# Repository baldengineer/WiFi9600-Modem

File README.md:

# WiFi9600 Modem
 Retro-cyling a Practical Peripherals 9600SA into a WiFiModem

Design files and code for WiFi9600.

As a kid, I had a Practical Peripherals 9600SA. For years I used it to connect to BBSes and then the Internet. At least, until I upgraded to a 56K USR Sportser.

This project removes the original electronics and replaces them with an ESP8266, MP3 Player, and some relays. It allows classic computers with a RS-232 port to connect to the internet via telnet. 

The MP3 player enables authentic fake modem sounds. And the relays are there for authentic real clicky-clicks.

Live stream archive of the project work is available here:
https://www.twitch.tv/baldengineer/videos

Watch the stream and help out in chat here:
https://twitch.tv/baldengineer

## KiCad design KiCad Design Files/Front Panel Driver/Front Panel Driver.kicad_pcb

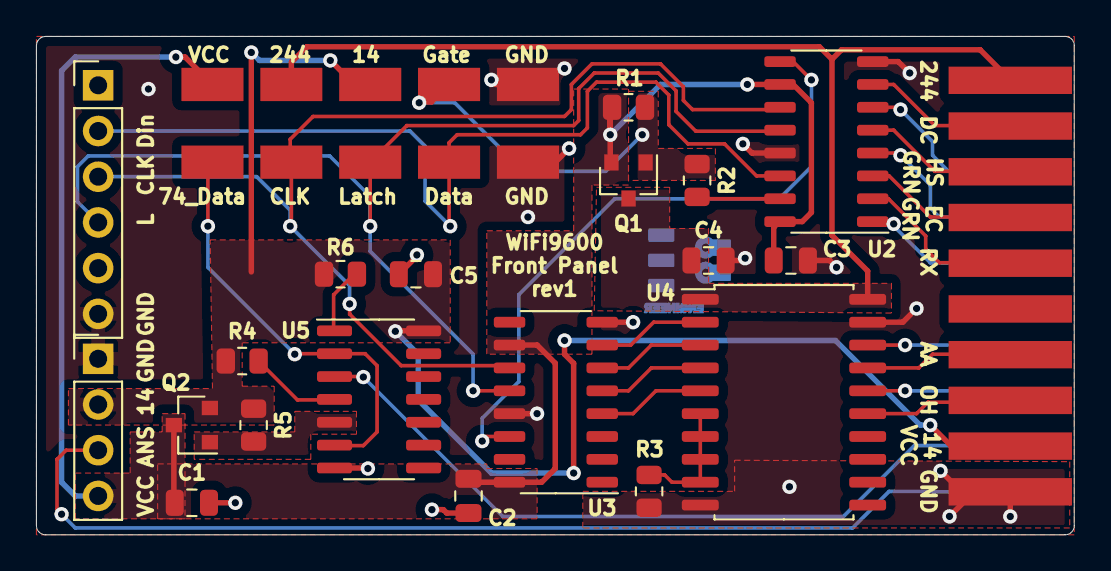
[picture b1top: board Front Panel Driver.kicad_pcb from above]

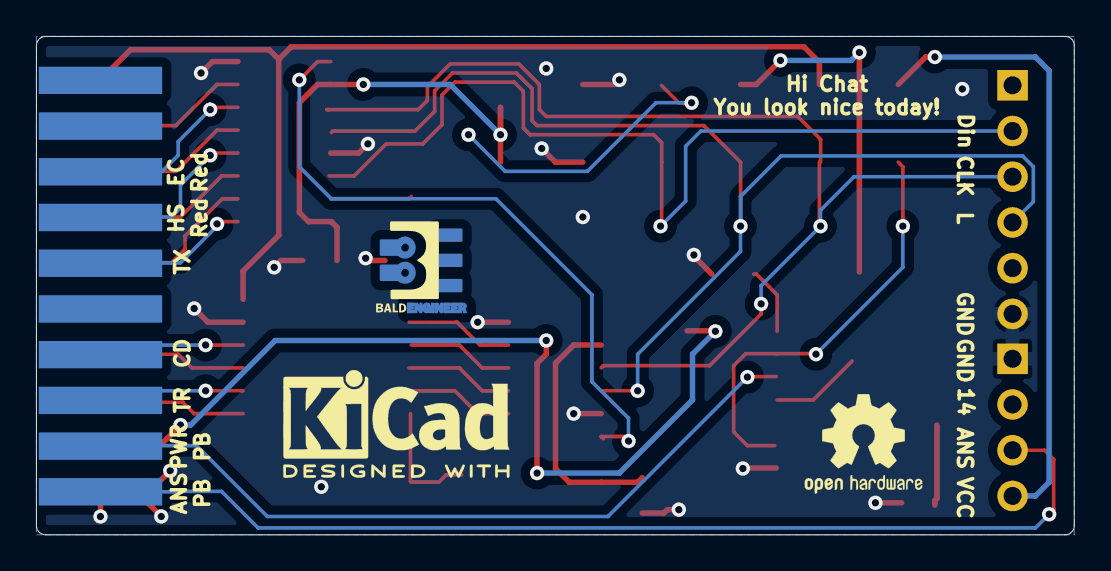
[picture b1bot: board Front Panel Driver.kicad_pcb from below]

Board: 2 copper layers, 57.7 x 27.7 mm, 31 parts (2 on the bottom side), 32 nets.

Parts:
C1, C2, C3, C4, C5: 1uF; C_0805_2012Metric
J9: Front_Panel; Edge_10mil_2x10
J10: PWR_HDR; PinHeader_1x04_P2.54mm_Vertical
J11: SH_HDR; PinHeader_1x06_P2.54mm_Vertical
Q1, Q2: P-NMOS; SOT-23
R1, R3, R4, R5, R6: 4k7; R_0805_2012Metric
R2: 1k; R_0805_2012Metric
TP1: TP_Panel_EN; Harwin-S1751-46-Test-Point
TP2: TP_244_VCC; Harwin-S1751-46-Test-Point
TP3: Data; Harwin-S1751-46-Test-Point
TP4: Clock; Harwin-S1751-46-Test-Point
TP5: Latch; Harwin-S1751-46-Test-Point
TP6: TP_74_Data; Harwin-S1751-46-Test-Point
TP7: TP_14_VCC; Harwin-S1751-46-Test-Point
TP8: TP_VCC; Harwin-S1751-46-Test-Point
TP9: TP_GND1; Harwin-S1751-46-Test-Point
TP10: TP_GND2; Harwin-S1751-46-Test-Point
U2, U3: 74HCT595; SO-16_3.9x9.9mm_P1.27mm
U4: 74HCT245; SOIC-20W_7.5x12.8mm_P1.27mm
U5: 74HCT74; SOIC-14_3.9x8.7mm_P1.27mm
svg2mod: G***; BE5

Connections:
/14-VCC: C5.1, J9.12, J10.2, Q2.2, R4.1, R5.1, R6.2, TP7.1, U5.14
/244-VCC: C4.1, J9.20, Q1.3, TP2.1, U4.1, U4.20
/AA: J9.14, U4.17
/ANS-PB: J9.10, J10.3
/CD: J9.7, U4.18
/DC: J9.19, U2.7
/Data-In: J11.2, TP3.1, U2.14
/EC-GRN: J9.17, U2.3
/EC-Red: J9.3, U2.6
/FF-DATA: TP6.1, U5.2, U5.6
/Gate244: Q1.1, R1.1, R2.1, TP1.1
/HS-GRN: J9.18, U2.5
/HS-Red: J9.4, U2.4
/Latch: J11.4, TP5.1, U2.12, U3.12
/OH: J9.13, U4.15
/PWR-PB: J9.9, U5.3
/Panel-En: R2.2, U2.15
/RX: J9.16, U2.2
/SH1: U3.4, U4.5
/SH2: U3.5, U4.4
/SH3: U3.6, U4.3
/SH4: U3.7, U4.2
/SH-Carry: U2.9, U3.14
/Ser-Clock: J11.3, TP4.1, U2.11, U3.11
/TR: J9.8, U4.16
/TX: J9.5, U2.1
GND: C1.2, C2.2, C3.2, C4.2, C5.2, J9.11, J10.1, J11.6, R3.2, TP9.1, TP10.1, U2.8, U2.13, U3.8, U3.13, U4.10, U4.19, U5.7
unnamed: Q2.1, R5.2, U5.5
unnamed: R3.1, U4.6, U4.7, U4.8, U4.9
unnamed: R4.2, U5.4
unnamed: R6.1, U5.1
VCC: C1.1, C2.1, C3.1, J10.4, Q1.2, Q2.3, R1.2, TP8.1, U2.10, U2.16, U3.10, U3.16

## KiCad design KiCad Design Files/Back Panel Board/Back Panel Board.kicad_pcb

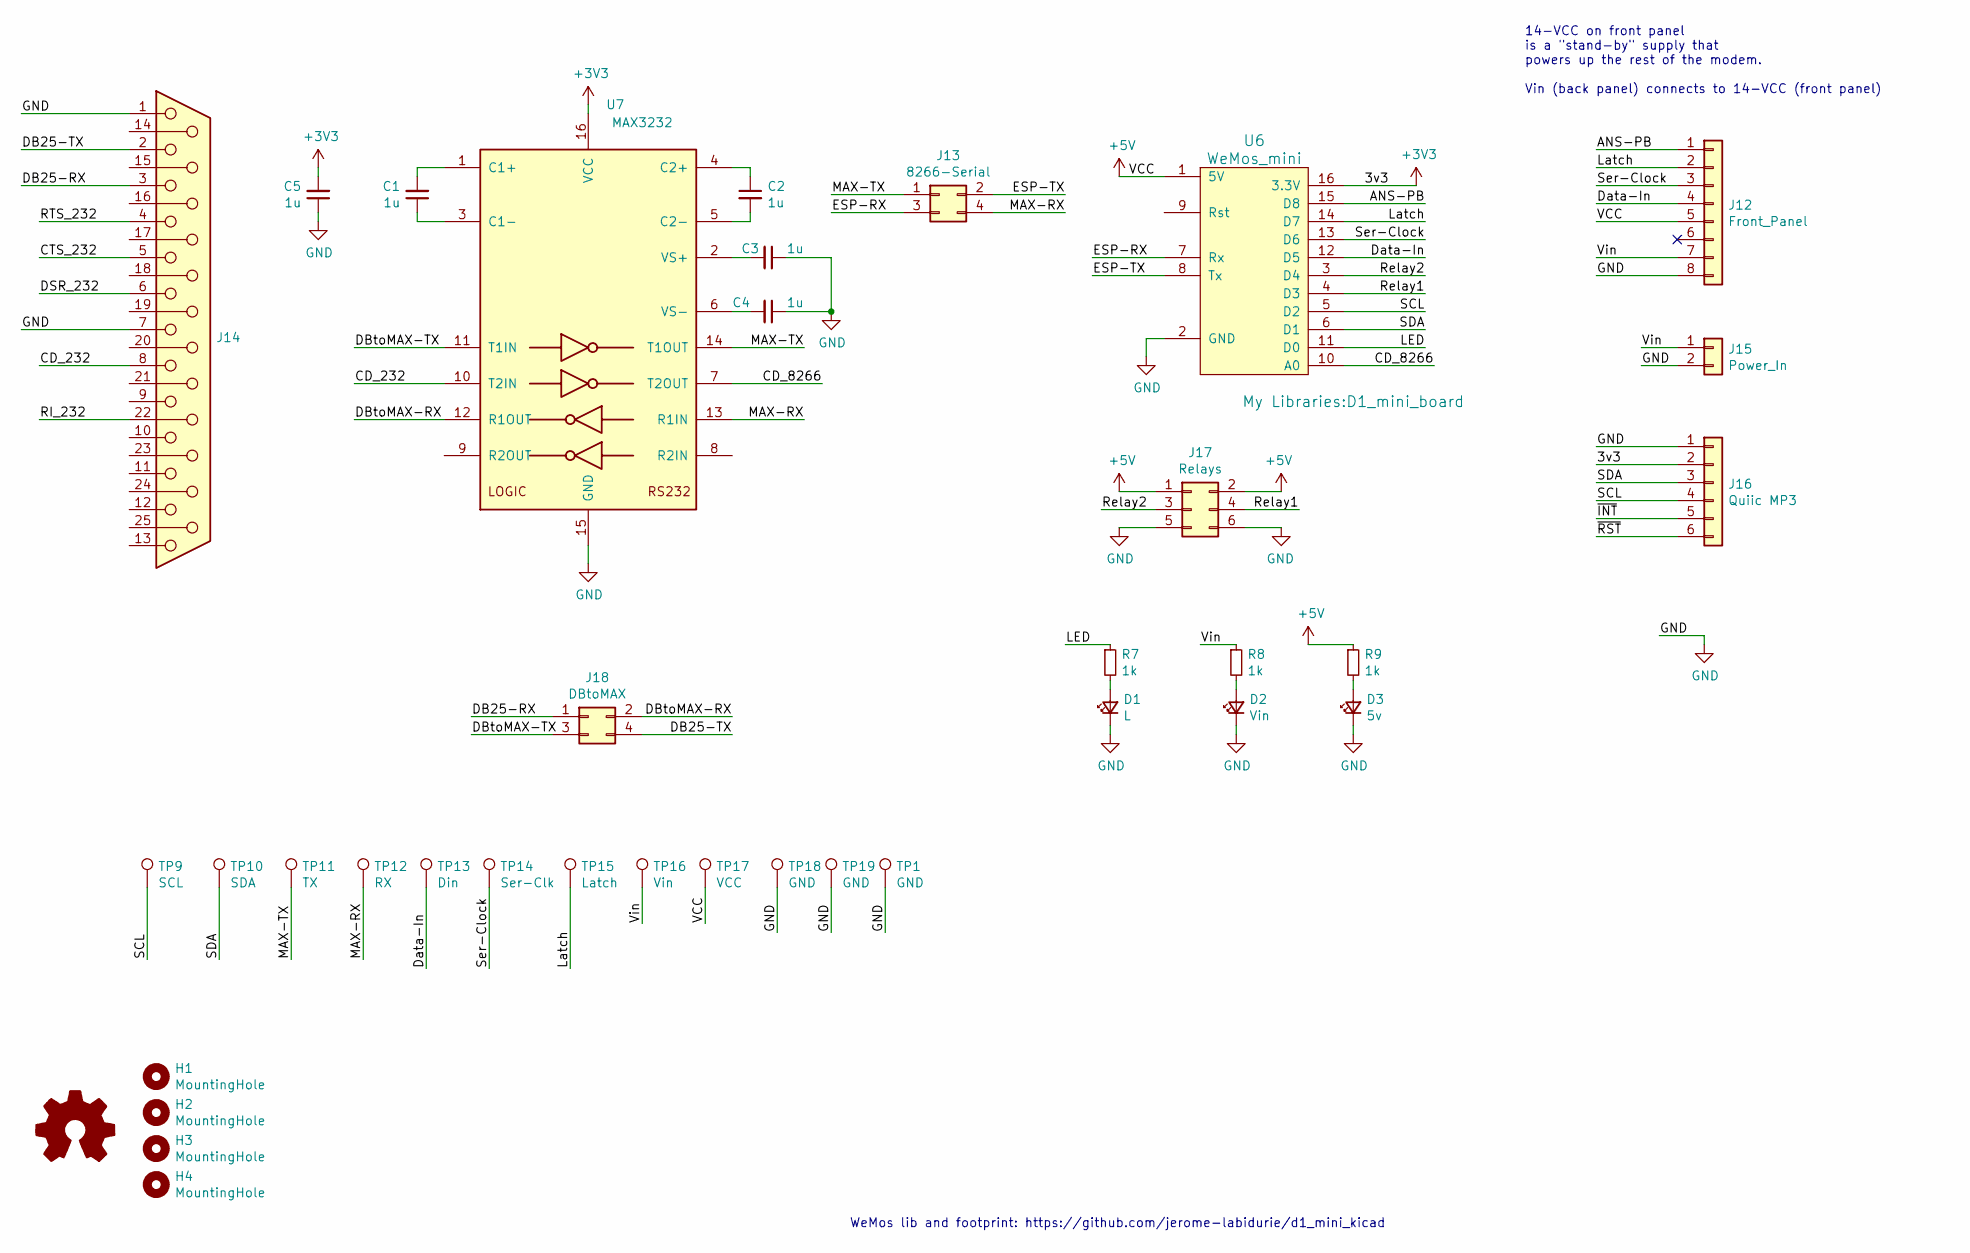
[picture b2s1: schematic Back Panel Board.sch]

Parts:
C1, C2, C3, C4, C5: 1u; C_0805_2012Metric
D1: L; LED_1206_3216Metric
D2: Vin; LED_1206_3216Metric
D3: 5v; LED_1206_3216Metric
H1, H2, H3, H4: MountingHole; MountingHole_2.5mm
J12: Front_Panel; PinHeader_1x08_P2.54mm_Vertical
J13: 8266-Serial; PinHeader_2x02_P2.54mm_Vertical
J14: DB25_Female_MountingHoles; DSUB-25_Female_EdgeMount_P2.77mm
J15: Power_In; PinHeader_1x02_P2.54mm_Vertical
J16: Quiic MP3; PinHeader_1x06_P2.54mm_Vertical
J17: Relays; PinHeader_2x03_P2.54mm_Vertical
J18: DBtoMAX; PinHeader_2x02_P2.54mm_Vertical
R7, R8, R9: 1k; R_0805_2012Metric
TP1, TP18, TP19: GND; Harwin-S1751-46-Test-Point
TP9: SCL; Harwin-S1751-46-Test-Point
TP10: SDA; Harwin-S1751-46-Test-Point
TP11: TX; Harwin-S1751-46-Test-Point
TP12: RX; Harwin-S1751-46-Test-Point
TP13: Din; Harwin-S1751-46-Test-Point
TP14: Ser-Clk; Harwin-S1751-46-Test-Point
TP15: Latch; Harwin-S1751-46-Test-Point
TP16: Vin; Harwin-S1751-46-Test-Point
TP17: VCC; Harwin-S1751-46-Test-Point
U6: WeMos_mini; D1_mini_board
U7: MAX3232; SOIC-16W_7.5x10.3mm_P1.27mm

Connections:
+3V3: C5.2, J16.2, U6.16 (3.3V), U7.16 (VCC)
+5V: J12.5, J17.1, J17.2, R9.1, TP17.1, U6.1 (5V)
/ANS-PB: J12.1, U6.15 (D8)
/CD_232: J14.8, U7.10 (T2IN)
/CD_8266: U6.10 (A0), U7.7 (T2OUT)
/CTS_232: J14.5
/DB25-RX: J14.3, J18.1
/DB25-TX: J14.2, J18.4
/DBtoMAX-RX: J18.2, U7.12 (R1OUT)
/DBtoMAX-TX: J18.3, U7.11 (T1IN)
/DSR_232: J14.6
/Data-In: J12.4, TP13.1, U6.12 (D5)
/ESP-RX: J13.3, U6.7 (Rx)
/ESP-TX: J13.2, U6.8 (Tx)
/LED: R7.1, U6.11 (D0)
/Latch: J12.2, TP15.1, U6.14 (D7)
/MAX-RX: J13.4, TP12.1, U7.13 (R1IN)
/MAX-TX: J13.1, TP11.1, U7.14 (T1OUT)
/RI_232: J14.22
/RTS_232: J14.4
/Relay1: J17.4, U6.4 (D3)
/Relay2: J17.3, U6.3 (D4)
/SCL: J16.4, TP9.1, U6.5 (D2)
/SDA: J16.3, TP10.1, U6.6 (D1)
/Ser-Clock: J12.3, TP14.1, U6.13 (D6)
/Vin: J12.7, J15.1, R8.1, TP16.1
/~INT: J16.5
/~RST: J16.6
GND: C3.1, C4.1, C5.1, D1.1 (K), D2.1 (K), D3.1 (K), J12.8, J14.1, J14.7, J15.2, J16.1, J17.5, J17.6, TP1.1, TP18.1, TP19.1, U6.2 (GND), U7.15 (GND)
unnamed: C1.1, U7.3 (C1-)
unnamed: C1.2, U7.1 (C1+)
unnamed: C2.1, U7.4 (C2+)
unnamed: C2.2, U7.5 (C2-)
unnamed: C3.2, U7.2 (VS+)
unnamed: C4.2, U7.6 (VS-)
unnamed: D1.2 (A), R7.2
unnamed: D2.2 (A), R8.2
unnamed: D3.2 (A), R9.2

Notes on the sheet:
14-VCC on front panel is a "stand-by" supply that powers up the rest of the modem. Vin (back panel) connects to 14-VCC (front panel)
WeMos lib and footprint: https://github.com/jerome-labidurie/d1_mini_kicad

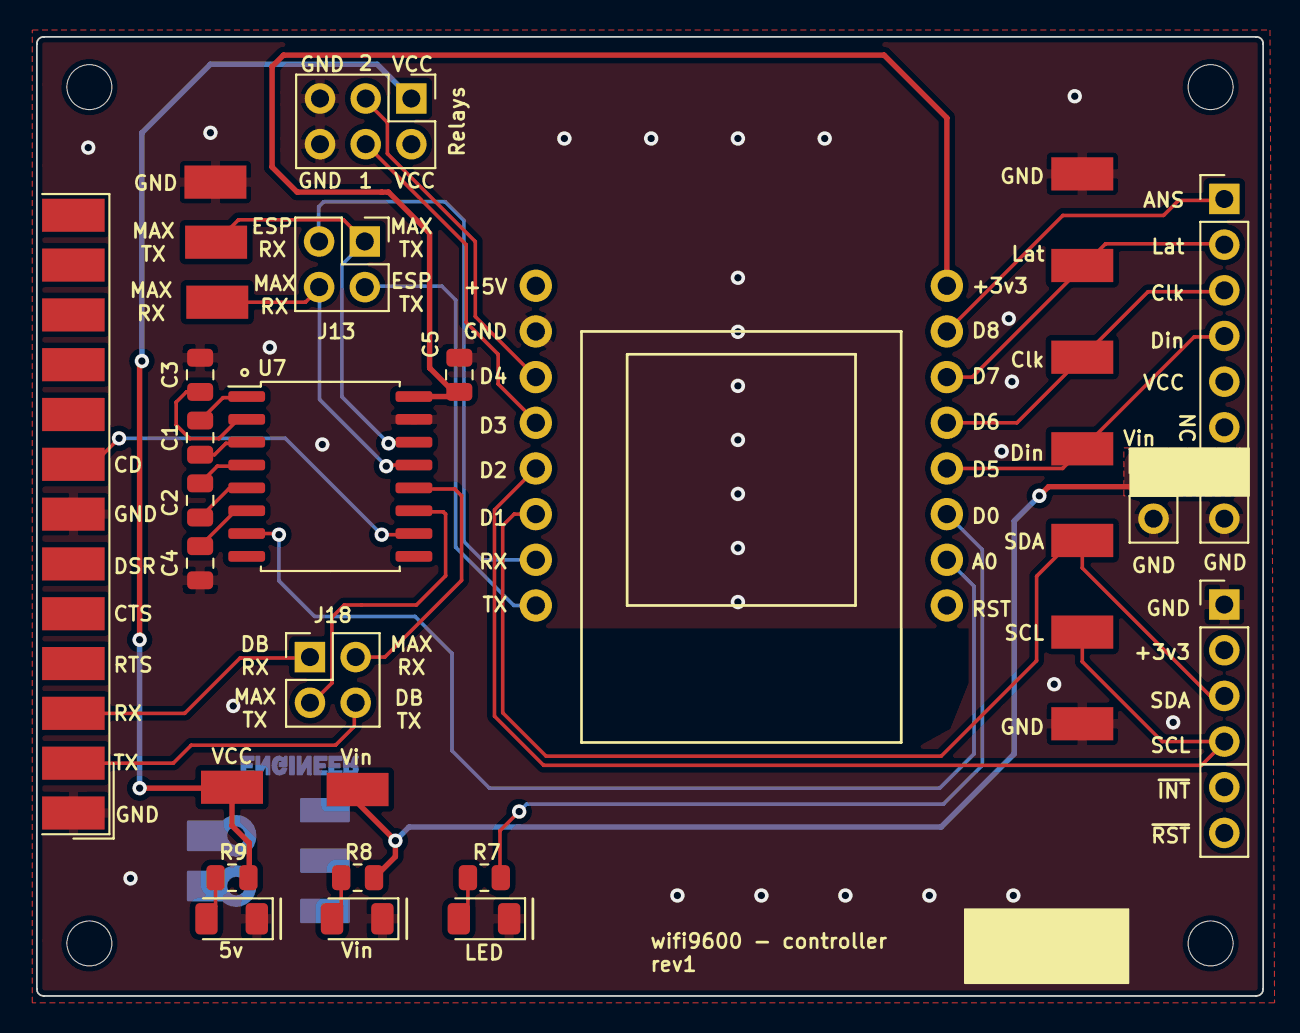
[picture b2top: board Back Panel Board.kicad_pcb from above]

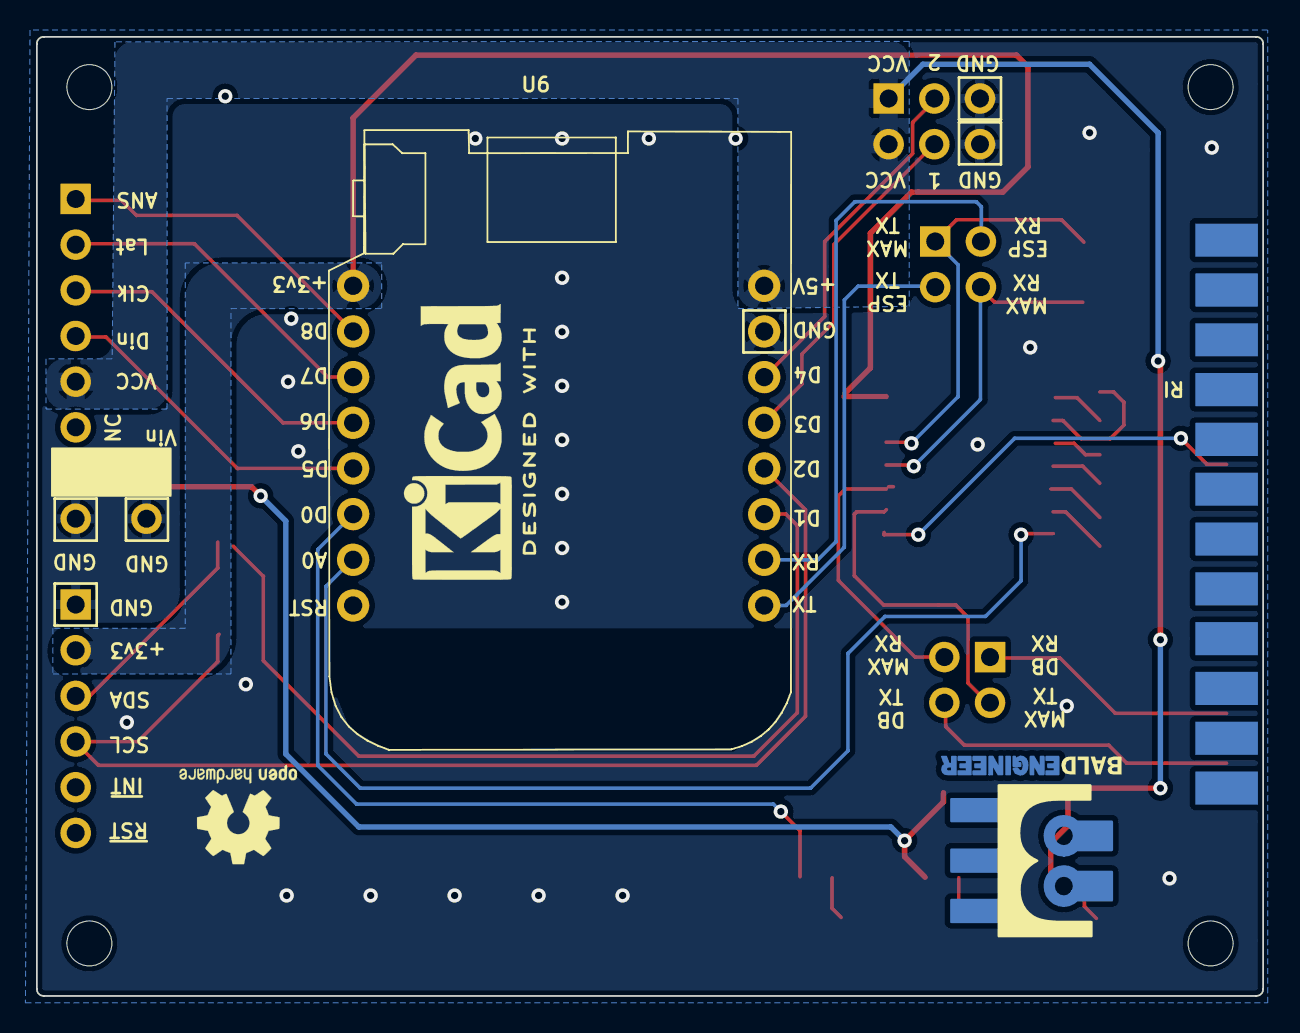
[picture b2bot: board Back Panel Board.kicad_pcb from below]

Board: 2 copper layers, 68.2 x 53.3 mm, 37 parts (2 on the bottom side), 32 nets.

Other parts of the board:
svg2mod: G***; BE10

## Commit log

2020-11-29 code for 2020-11-29 stream start
2020-11-29 before integrating FP MP3 code
2020-11-29 Post-stream
    Combined code from previous streams and identified spots to control the LEDs. Blocked by bad Wemos modules. (Logic side of 8266 works, but the WiFi radio isn't functioning.)
2020-12-03 lights and sound all work
2020-12-04 front-panel behavior
    changed TR to turn-on when modem is ready. added some extra delay for TX (but still not quite right.)
2020-12-04 ans pb disconnects modem
    Add same functionality as original modem. When a connection is active, the "answer" button disconnects the modem.
2020-12-04 Changed default response
    Defaults to CONNECT XXXX message type. Same as running "atx1."
2020-12-10 kicad files with v1 mistakes
2021-03-22 code clean up
